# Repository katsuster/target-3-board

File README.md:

# target-3-board

`target-3` is an open-source machine that raises knockdown targets for shooting.

This repository contains the KiCad data of the boards for `target-3`.
The boards hold the microcontroller boards, supply power, and connect them with the servo motors and the push button.

Please refer to these repositories if you are interested in other modules of `target-3`.

* Remote: https://github.com/katsuster/target-3-remote
* Server: https://github.com/katsuster/target-3-server

## Requires

* Software
  * KiCad 10.0

## How to use

TBD

## Source structures

* remote/
  * Remote controller board, holds the remote microcontroller board (e.g. M5Stamp C3)
  * Supplies power to the microcontroller board
  * Has a connector for an external push button
* server/
  * Server board, holds the server microcontroller board (e.g. M5Stamp C3)
  * Sends PWM signals and power enable signals to the motor driver boards
* motor/
  * Motor driver board, used to drive servo motors
  * Supplies power to the servo motors through its own power switch
  * Passes the PWM signals from the server board through to the servo motors

## Other documents

* [Parts list](doc/parts_jlcpcb.md)

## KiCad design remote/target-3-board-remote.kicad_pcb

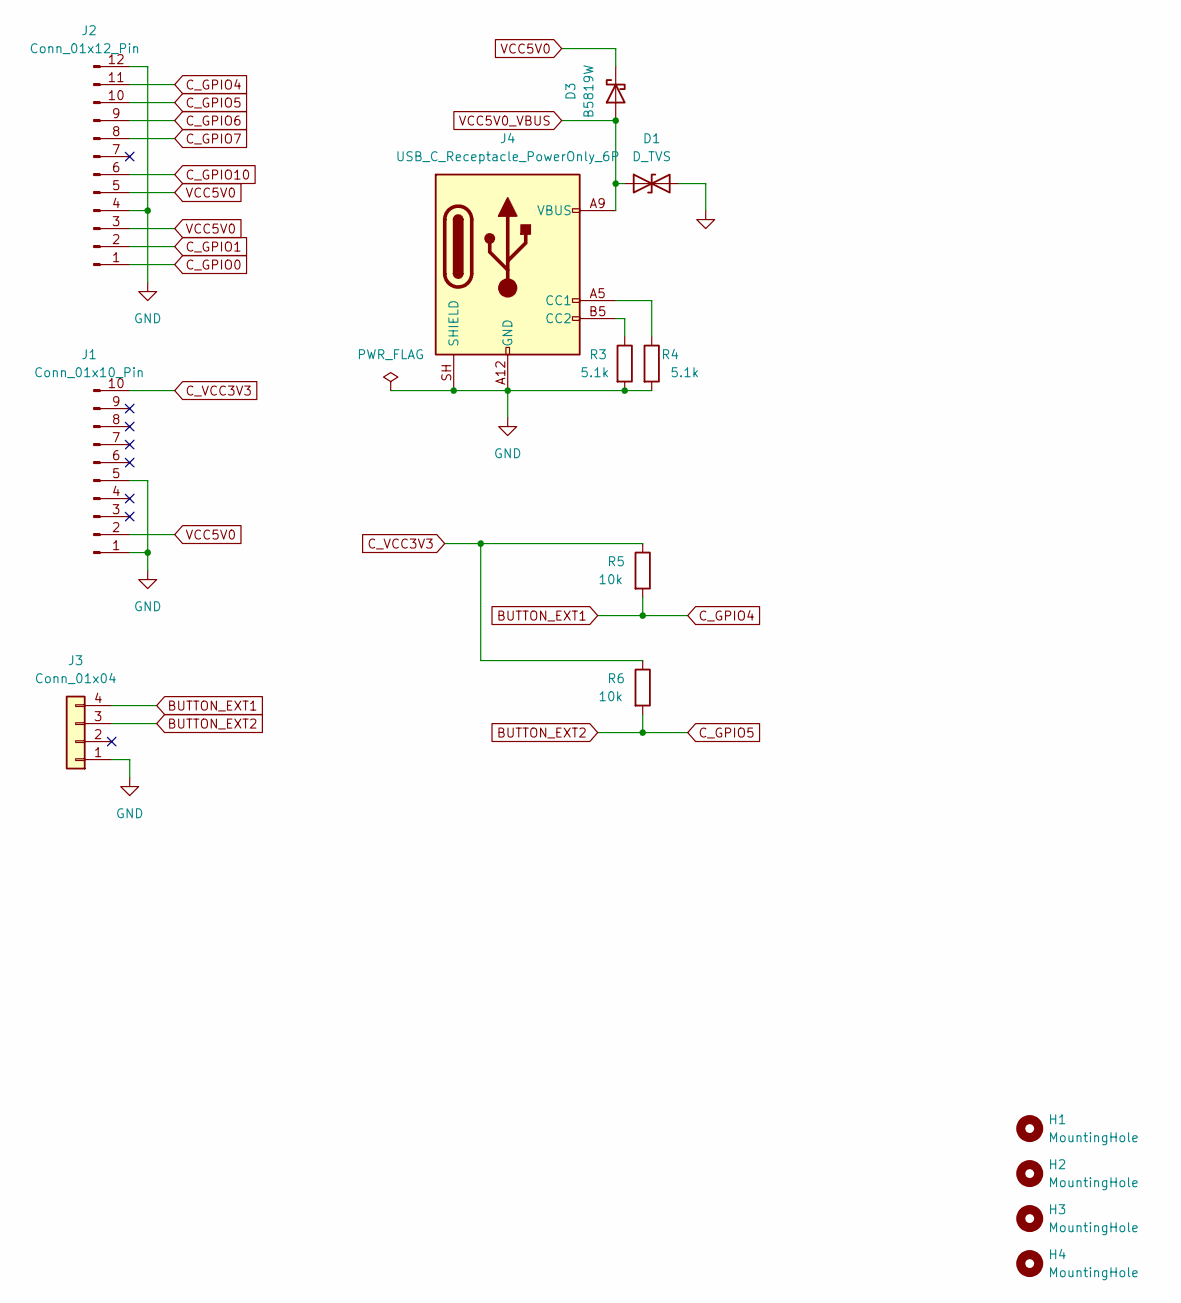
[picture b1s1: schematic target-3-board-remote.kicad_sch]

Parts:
D1: D_TVS; D_SOD-323; LCSC C177022
D3: B5819W; D_SOD-123
H1, H2, H3, H4: MountingHole; MountingHole_3.2mm_M3_ISO14580
J1: Conn_01x10_Pin; PinHeader_1x10_P2.54mm_Vertical
J2: Conn_01x12_Pin; PinHeader_1x12_P2.54mm_Vertical
J3: Conn_01x04; JST_XH_S4B-XH-A_1x04_P2.50mm_Horizontal
J4: USB_C_Receptacle_PowerOnly_6P; USB_C_Receptacle_GCT_USB4125-xx-x_6P_TopMnt_Horizontal
R3, R4: 5.1k; R_0603_1608Metric
R5, R6: 10k; R_0603_1608Metric

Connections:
BUTTON_EXT1: J2.11, J3.4, R5.2
BUTTON_EXT2: J2.10, J3.3, R6.2
C_GPIO0: J2.1
C_GPIO1: J2.2
C_GPIO6: J2.9
C_GPIO7: J2.8
C_GPIO10: J2.6
C_VCC3V3: J1.10, R5.1, R6.1
GND: D1.2 (A2), J1.1, J1.5, J2.4, J2.12, J3.1, J4.A12 (GND), J4.B12 (GND), J4.SH (SHIELD), R3.2, R4.2
unnamed: J4.A5 (CC1), R4.1
unnamed: J4.B5 (CC2), R3.1
VCC5V0: D3.1 (K), J1.2, J2.3, J2.5
VCC5V0_VBUS: D1.1 (A1), D3.2 (A), J4.A9 (VBUS), J4.B9 (VBUS)

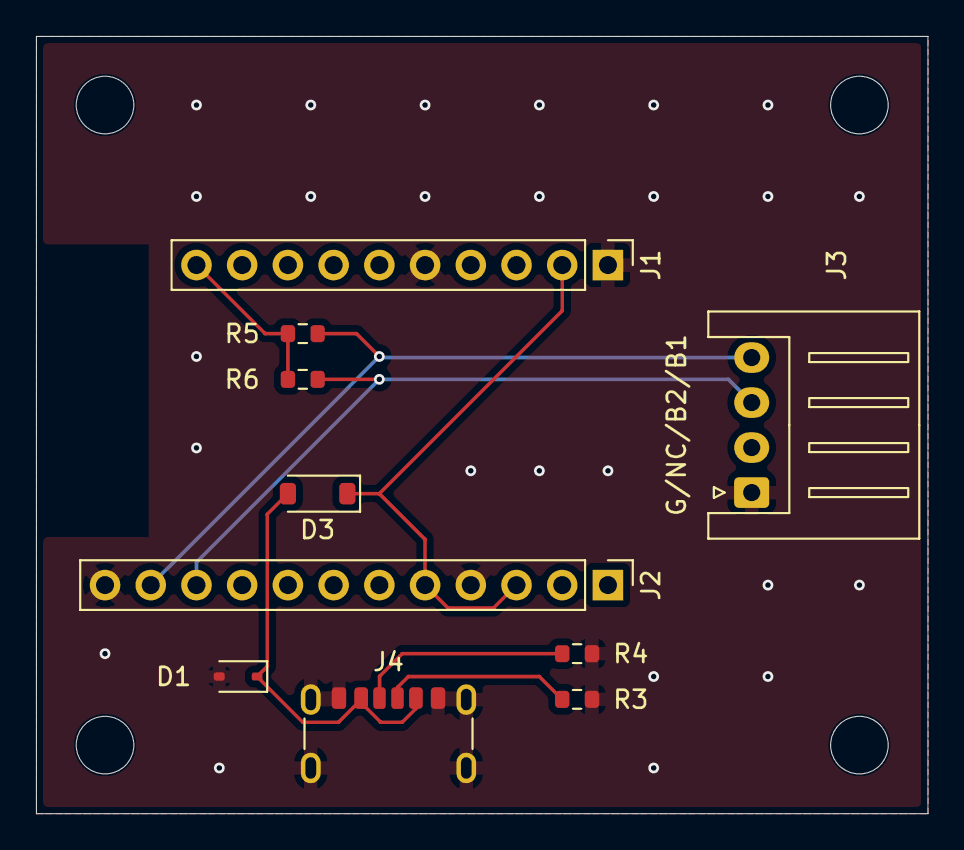
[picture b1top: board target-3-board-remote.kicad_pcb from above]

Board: 2 copper layers, 49.5 x 43.2 mm, 14 parts (0 on the bottom side), 8 nets.

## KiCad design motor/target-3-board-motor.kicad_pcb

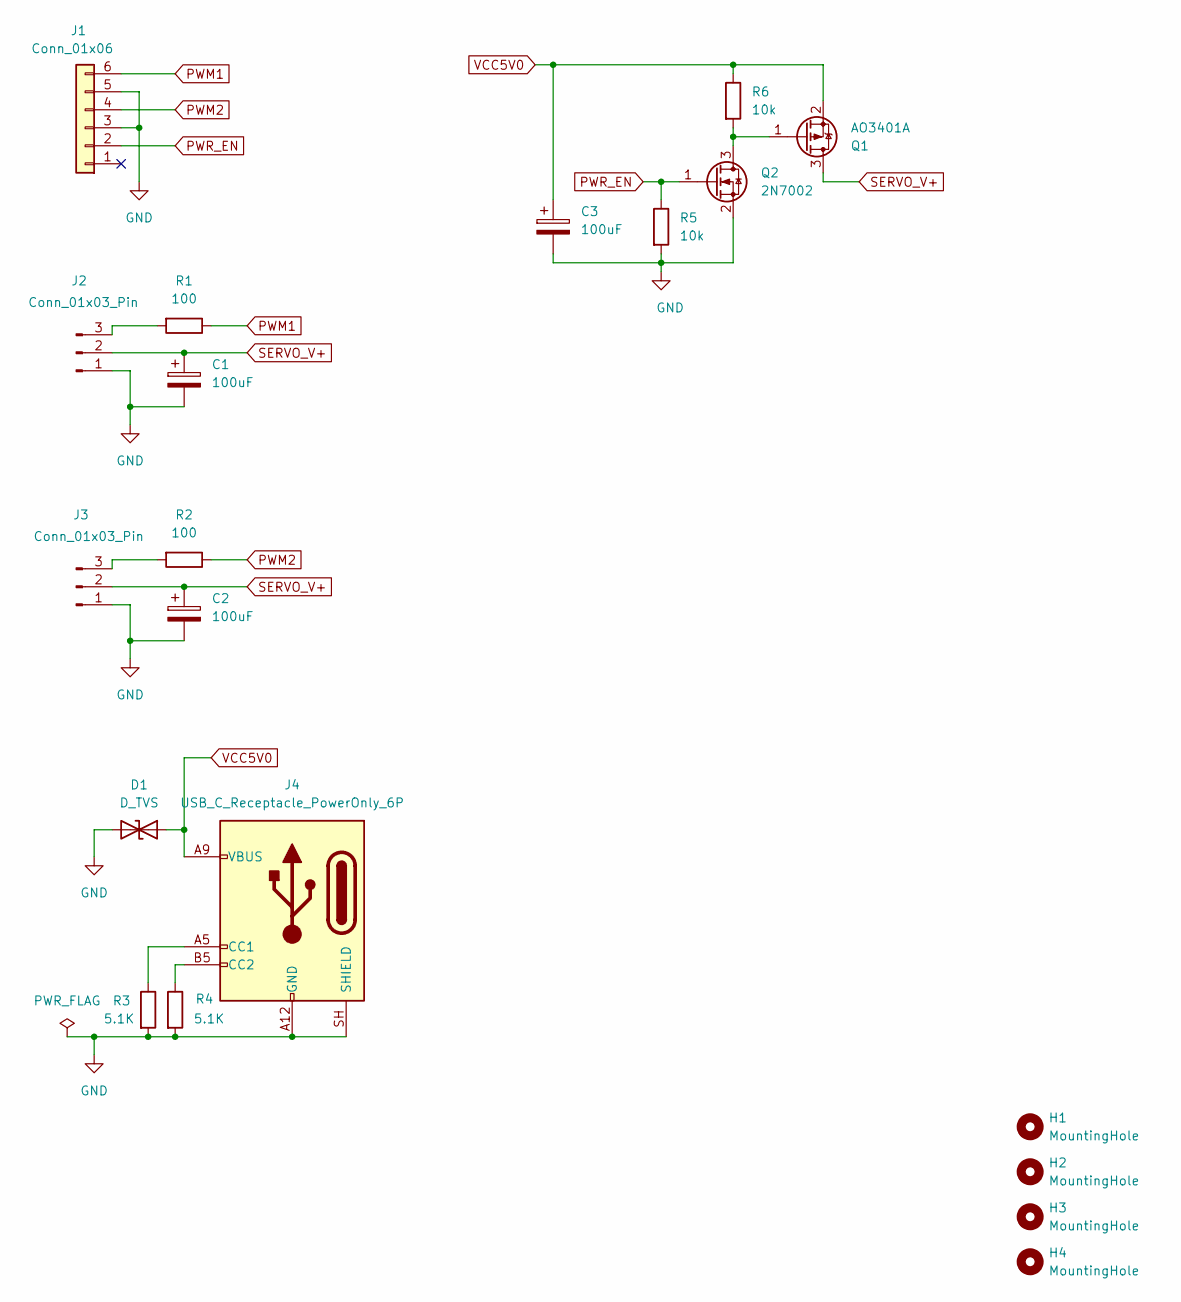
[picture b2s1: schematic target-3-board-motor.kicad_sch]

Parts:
C1, C2, C3: 100uF; CP_Elec_6.3x7.7
D1: D_TVS; D_SOD-323; LCSC C177022
H1, H2, H3, H4: MountingHole; MountingHole_3.2mm_M3_ISO14580
J1: Conn_01x06; JST_XH_S6B-XH-A_1x06_P2.50mm_Horizontal
J2, J3: Conn_01x03_Pin; PinHeader_1x03_P2.54mm_Horizontal
J4: USB_C_Receptacle_PowerOnly_6P; USB_C_Receptacle_GCT_USB4125-xx-x_6P_TopMnt_Horizontal
Q1: AO3401A; SOT-23
Q2: 2N7002; SOT-23
R1, R2: 100; R_0603_1608Metric
R3, R4: 5.1K; R_0603_1608Metric
R5, R6: 10k; R_0603_1608Metric

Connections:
GND: C1.2, C2.2, C3.2, D1.2 (A2), J1.3, J1.5, J2.1, J3.1, J4.A12 (GND), J4.B12 (GND), J4.SH (SHIELD), Q2.2 (S), R3.2, R4.2, R5.2
unnamed: J2.3, R1.2
unnamed: J3.3, R2.2
unnamed: J4.A5 (CC1), R3.1
unnamed: J4.B5 (CC2), R4.1
unnamed: Q1.1 (G), Q2.3 (D), R6.2
PWM1: J1.6, R1.1
PWM2: J1.4, R2.1
PWR_EN: J1.2, Q2.1 (G), R5.1
SERVO_V+: C1.1, C2.1, J2.2, J3.2, Q1.3 (D)
VCC5V0: C3.1, D1.1 (A1), J4.A9 (VBUS), J4.B9 (VBUS), Q1.2 (S), R6.1

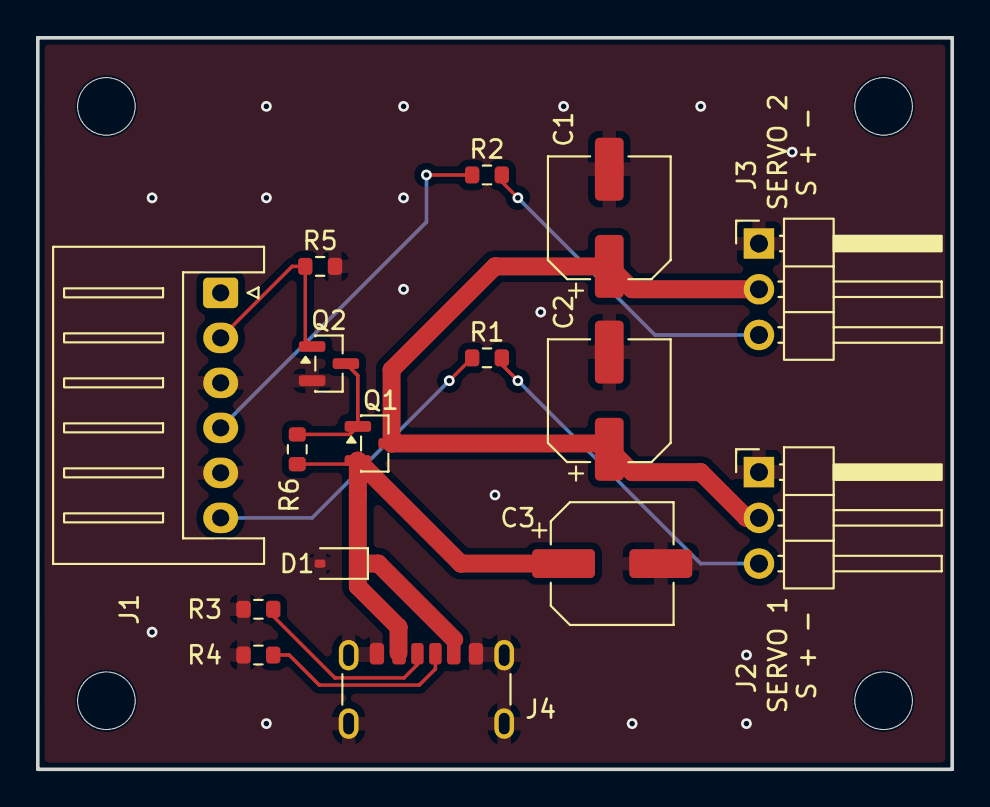
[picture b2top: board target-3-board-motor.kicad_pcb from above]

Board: 2 copper layers, 50.8 x 40.6 mm, 20 parts (0 on the bottom side), 11 nets.

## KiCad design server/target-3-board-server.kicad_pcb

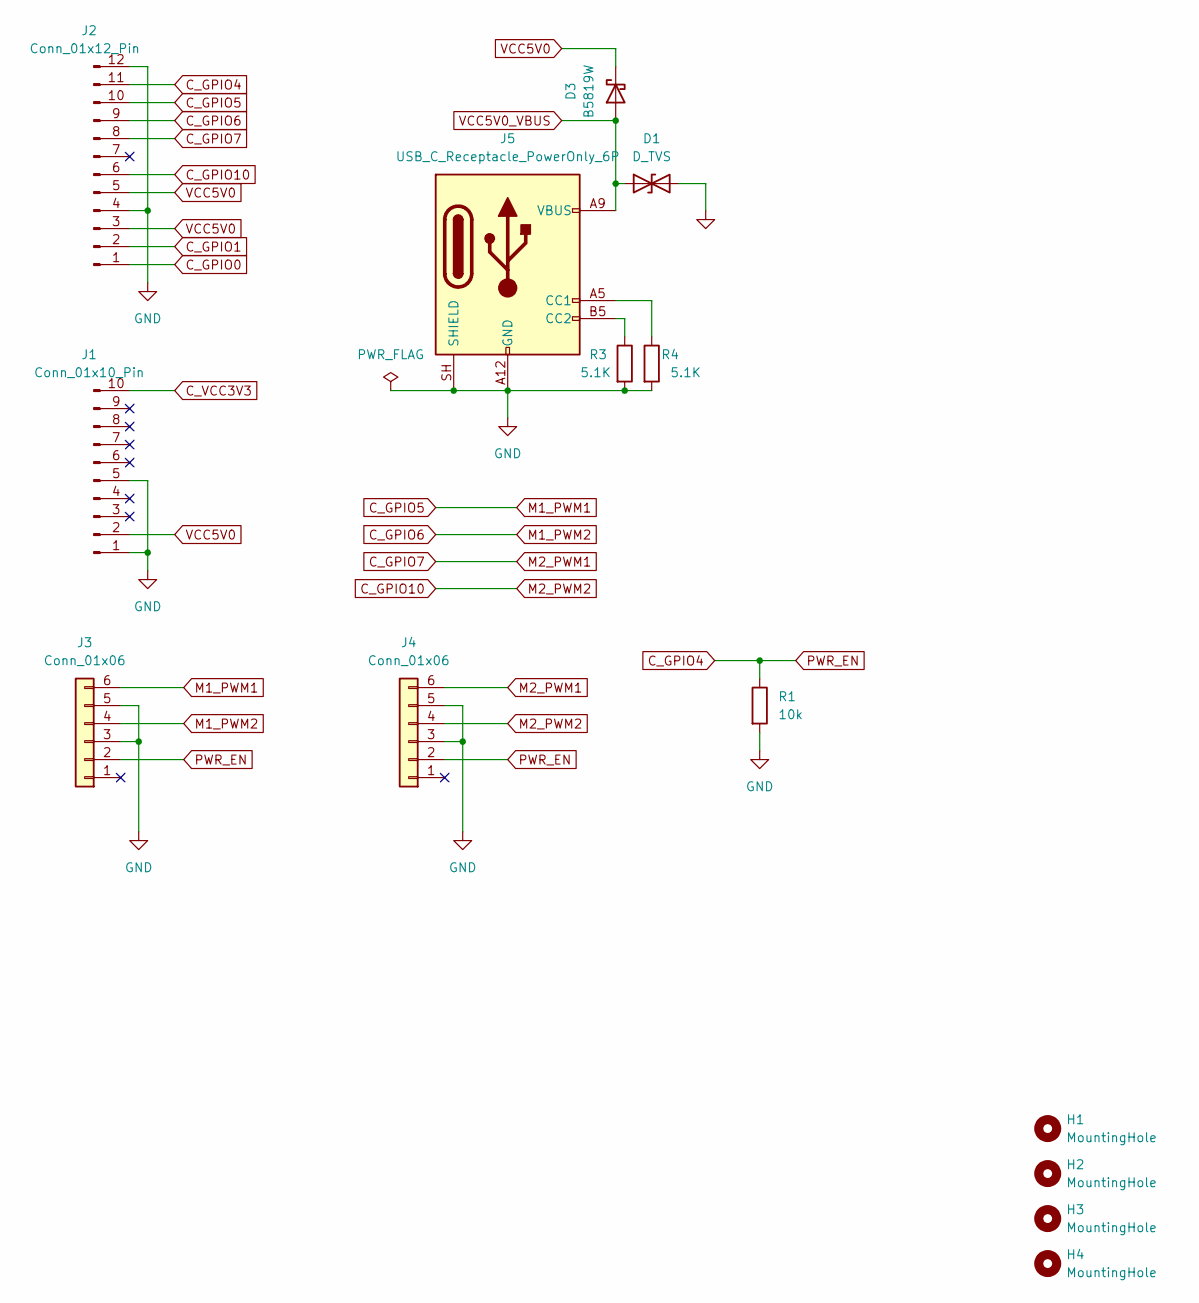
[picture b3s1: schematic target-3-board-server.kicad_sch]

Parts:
D1: D_TVS; D_SOD-323; LCSC C177022
D3: B5819W; D_SOD-123
H1, H2, H3, H4: MountingHole; MountingHole_3.2mm_M3_ISO14580
J1: Conn_01x10_Pin; PinHeader_1x10_P2.54mm_Vertical
J2: Conn_01x12_Pin; PinHeader_1x12_P2.54mm_Vertical
J3, J4: Conn_01x06; JST_XH_S6B-XH-A_1x06_P2.50mm_Horizontal
J5: USB_C_Receptacle_PowerOnly_6P; USB_C_Receptacle_GCT_USB4125-xx-x_6P_TopMnt_Horizontal
R1: 10k; R_0603_1608Metric
R3, R4: 5.1K; R_0603_1608Metric

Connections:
C_GPIO0: J2.1
C_GPIO1: J2.2
C_GPIO4: J2.11, J3.2, J4.2, R1.1
C_GPIO5: J2.10, J3.6
C_GPIO6: J2.9, J3.4
C_GPIO7: J2.8, J4.6
C_GPIO10: J2.6, J4.4
C_VCC3V3: J1.10
GND: D1.2 (A2), J1.1, J1.5, J2.4, J2.12, J3.3, J3.5, J4.3, J4.5, J5.A12 (GND), J5.B12 (GND), J5.SH (SHIELD), R1.2, R3.2, R4.2
unnamed: J5.A5 (CC1), R4.1
unnamed: J5.B5 (CC2), R3.1
VCC5V0: D3.1 (K), J1.2, J2.3, J2.5
VCC5V0_VBUS: D1.1 (A1), D3.2 (A), J5.A9 (VBUS), J5.B9 (VBUS)

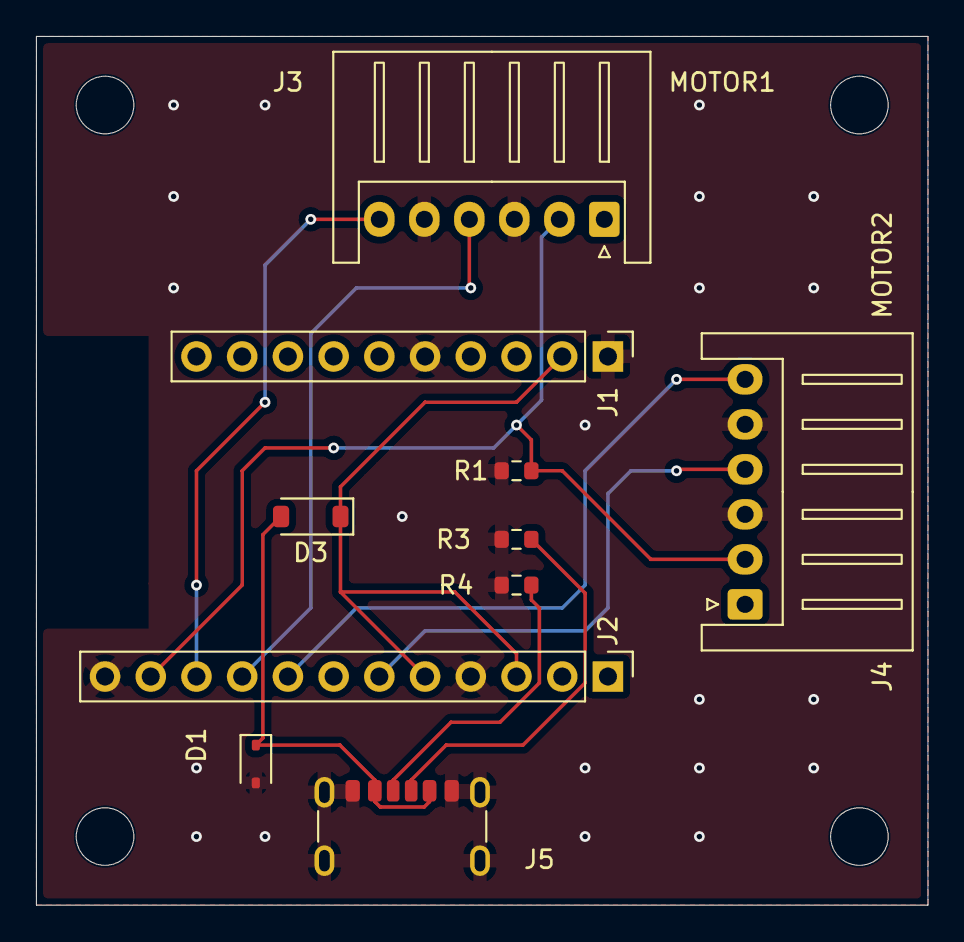
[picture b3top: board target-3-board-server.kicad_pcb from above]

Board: 2 copper layers, 49.5 x 48.3 mm, 14 parts (0 on the bottom side), 10 nets.
